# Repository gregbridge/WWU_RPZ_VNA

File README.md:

# WWU_RPZ_VNA
Low Cost VNA running on a Raspberry Pi Zero running Raspbian Stretch. Paired with appropriate circuitry and soundcard for A to D conversion.

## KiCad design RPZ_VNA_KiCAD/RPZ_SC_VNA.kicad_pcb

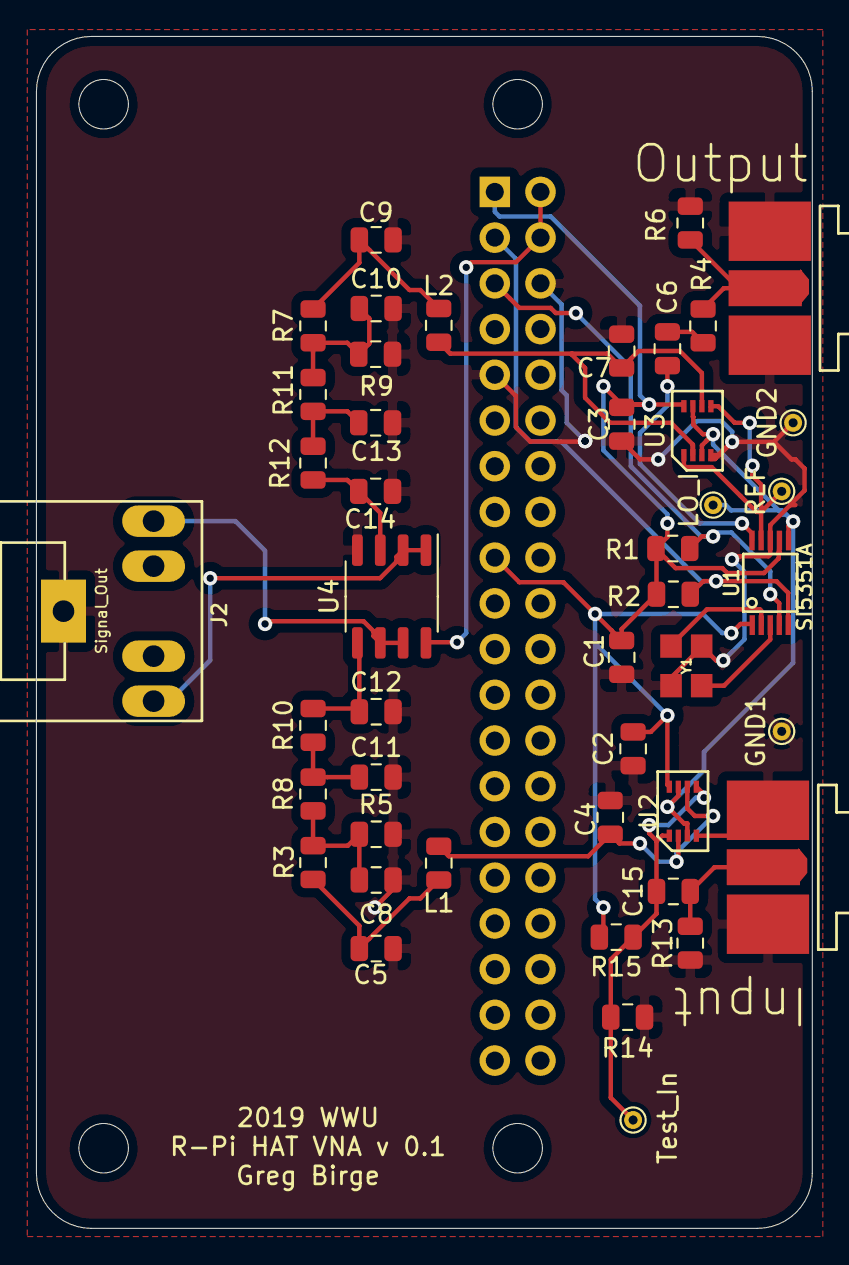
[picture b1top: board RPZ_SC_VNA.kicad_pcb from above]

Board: 2 copper layers, 43.1 x 66.2 mm, 46 parts (1 on the bottom side), 26 nets.

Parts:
C1, C2, C3: 0.1uF; C_0805_2012Metric
C4, C7: .005uF; C_0805_2012Metric
C5, C9: 680nF; C_0805_2012Metric
C6, C15: 1.0uF; C_0805_2012Metric
C8, C10: 10nF; C_0805_2012Metric
C11, C12, C13, C14: 1nF; C_0805_2012Metric
GND1: GND1; TestPoint_THTPad_D1.0mm_Drill0.5mm
GND2: GND2; TestPoint_THTPad_D1.0mm_Drill0.5mm
Input1: P1; SMA_EDGE
J2: Signal_Out; Tayda_3.5mm_stereo_TRS_jack_A-853
Jr: GPIO Header; Raspberry_Pi_Zero_Socketed_THT_FaceDown_MountingHoles
L1, L2: 100uH; L_0805_2012Metric
LO_I: LO_I; TestPoint_THTPad_D1.0mm_Drill0.5mm
Output1: P2; SMA_EDGE
R1, R2: 4.7k; R_0805_2012Metric
R3, R7: 10k; R_0805_2012Metric
R4, R6: R; R_0805_2012Metric
R5, R9: 30k; R_0805_2012Metric
R8, R11: 51k; R_0805_2012Metric
R10, R12: 1M; R_0805_2012Metric
R13: 56; R_0805_2012Metric
R14: 220k; R_0805_2012Metric
R15: 39k; R_0805_2012Metric
REF: REF; TestPoint_THTPad_D1.0mm_Drill0.5mm
Test_In: Test_IN; TestPoint_THTPad_D1.0mm_Drill0.5mm
U1: SI5351A; MSOP-10
U2, U3: NL7WB66; VFSOP-8
U4: LM2904; SO-8_3.9x4.9mm_P1.27mm
Y1: CX3225

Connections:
+3V3: C1.2, C2.1, C3.1, Jr.1, Jr.17, R1.2, R2.2, R15.2, U1.1, U1.7, U2.8, U3.8
+5V: Jr.2, Jr.4, U4.8
/LO_I: LO_I.1, U1.6, U2.3, U2.7, U3.3, U3.7
/SCL: Jr.5, R1.1, U1.4
/SDA: Jr.3, R2.1, U1.5
GND: C1.1, C2.2, C3.2, C4.1, C5.2, C7.1, C8.2, C9.2, C10.2, C11.2, C12.2, C13.2, C14.2, GND1.1, GND2.1, Input1.2, J2.1, Jr.6, Jr.9, Output1.2, R5.2, R6.2, R9.2, R13.2, R14.2, U1.8, U2.4, U3.4, U4.4, Y1.2, Y1.4
unnamed: C4.2, L1.1, U2.2, U2.6
unnamed: C5.1, L1.2, R3.2
unnamed: C6.1, R4.2
unnamed: C6.2, U1.10
unnamed: C7.2, L2.1, U3.2, U3.6
unnamed: C8.1, R3.1, R5.1, R8.1
unnamed: C9.1, L2.2, R7.2
unnamed: C10.1, R7.1, R9.1, R11.1
unnamed: C11.1, R8.2, R10.1
unnamed: C12.1, R10.2, U4.5
unnamed: C13.1, R11.2, R12.1
unnamed: C14.1, R12.2, U4.3
unnamed: C15.1, R14.1, R15.1, Test_In.1, U2.1, U2.5
unnamed: C15.2, Input1.1, R13.1
unnamed: J2.2, U4.6, U4.7
unnamed: J2.3, U4.1, U4.2
unnamed: Output1.1, R4.1, R6.1
unnamed: REF.1, U1.9, U3.1, U3.5
unnamed: U1.2, Y1.3
unnamed: U1.3, Y1.1

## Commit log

2019-05-09 First commit, added example code
2019-05-09 Added Library List and set_frequency function to python script
2019-05-09 Added Config file for constants
2019-05-09 Added setup shell script
2019-05-09 Switch apt-gets to pip3 cmds
2019-05-09 Have rough FFT plot, config.py does not accept fs=96k
2019-05-09 Duplicated and renamed primary function for TF plotting
2019-05-09 Corrected Sample rate in config file
2019-05-09 Made sigRec actual test. Have rudimentary bode plots but terrible runtime
2019-05-09 Removed fft commands and used only H(K) method from Frohne, decreased sample size
2019-05-09 Added small test commands to simply toggle output signal on and off for testing
2019-05-09 Cleaned up code and removed old comments
2019-05-10 Added Arg parsing to sigRec, beginning to sweep frequencies with tfPlot
2019-05-10 Added time measuring to all over TFplot, copied down error text
2019-05-10 Plotting 30 points in tf, have test results, more comments on sigRec
2019-05-10 Consolidating files in subdirectory
2019-05-13 Adding Initial KiCAD Project
2019-05-13 Finished Schematic V1.0 and added necessary symbols/footprints
2019-05-13 Flipped Audio Jack, put Test on Tip, Ref on Ring
2019-05-14 Actually pushing the changes, forgot to hit Ctrl-S
2019-05-15 Built PCB, has conflicts with Raspberry Pi Zero Footprint. Smaller Pads and maybe increase size of PCB
2019-05-17 Finished PCB 1.0 and created respective gerber files and zipped 'em
2019-05-17 Forgot to Ctrl-S a couple things
2019-05-20 Added BOM Version 1 that does not include resistors/capacitors/things we have in lab/ etc
2019-06-11 Creating Python folder
2019-06-11 Added adafruit-blinka
